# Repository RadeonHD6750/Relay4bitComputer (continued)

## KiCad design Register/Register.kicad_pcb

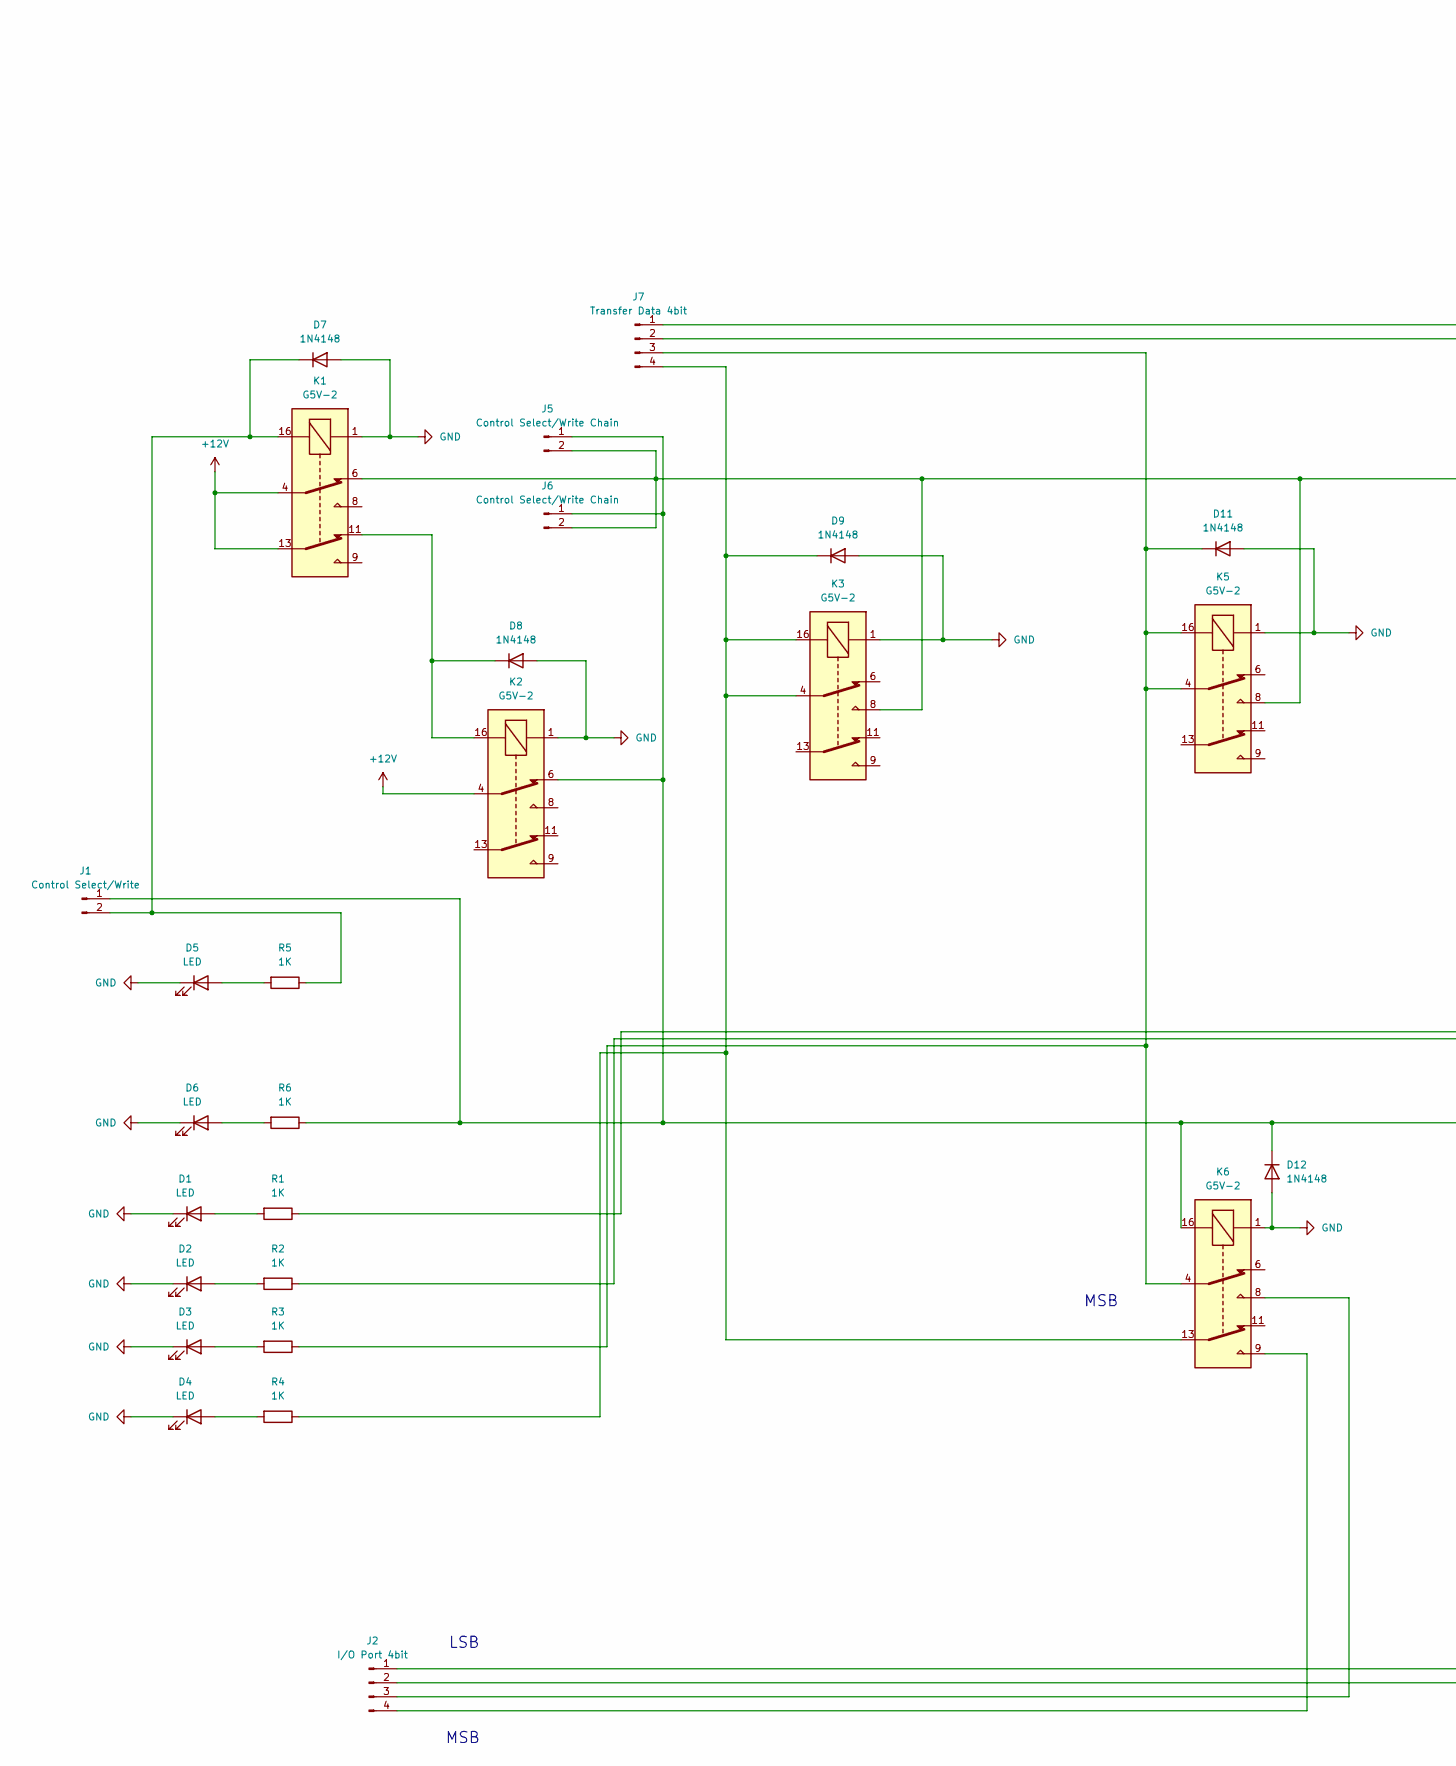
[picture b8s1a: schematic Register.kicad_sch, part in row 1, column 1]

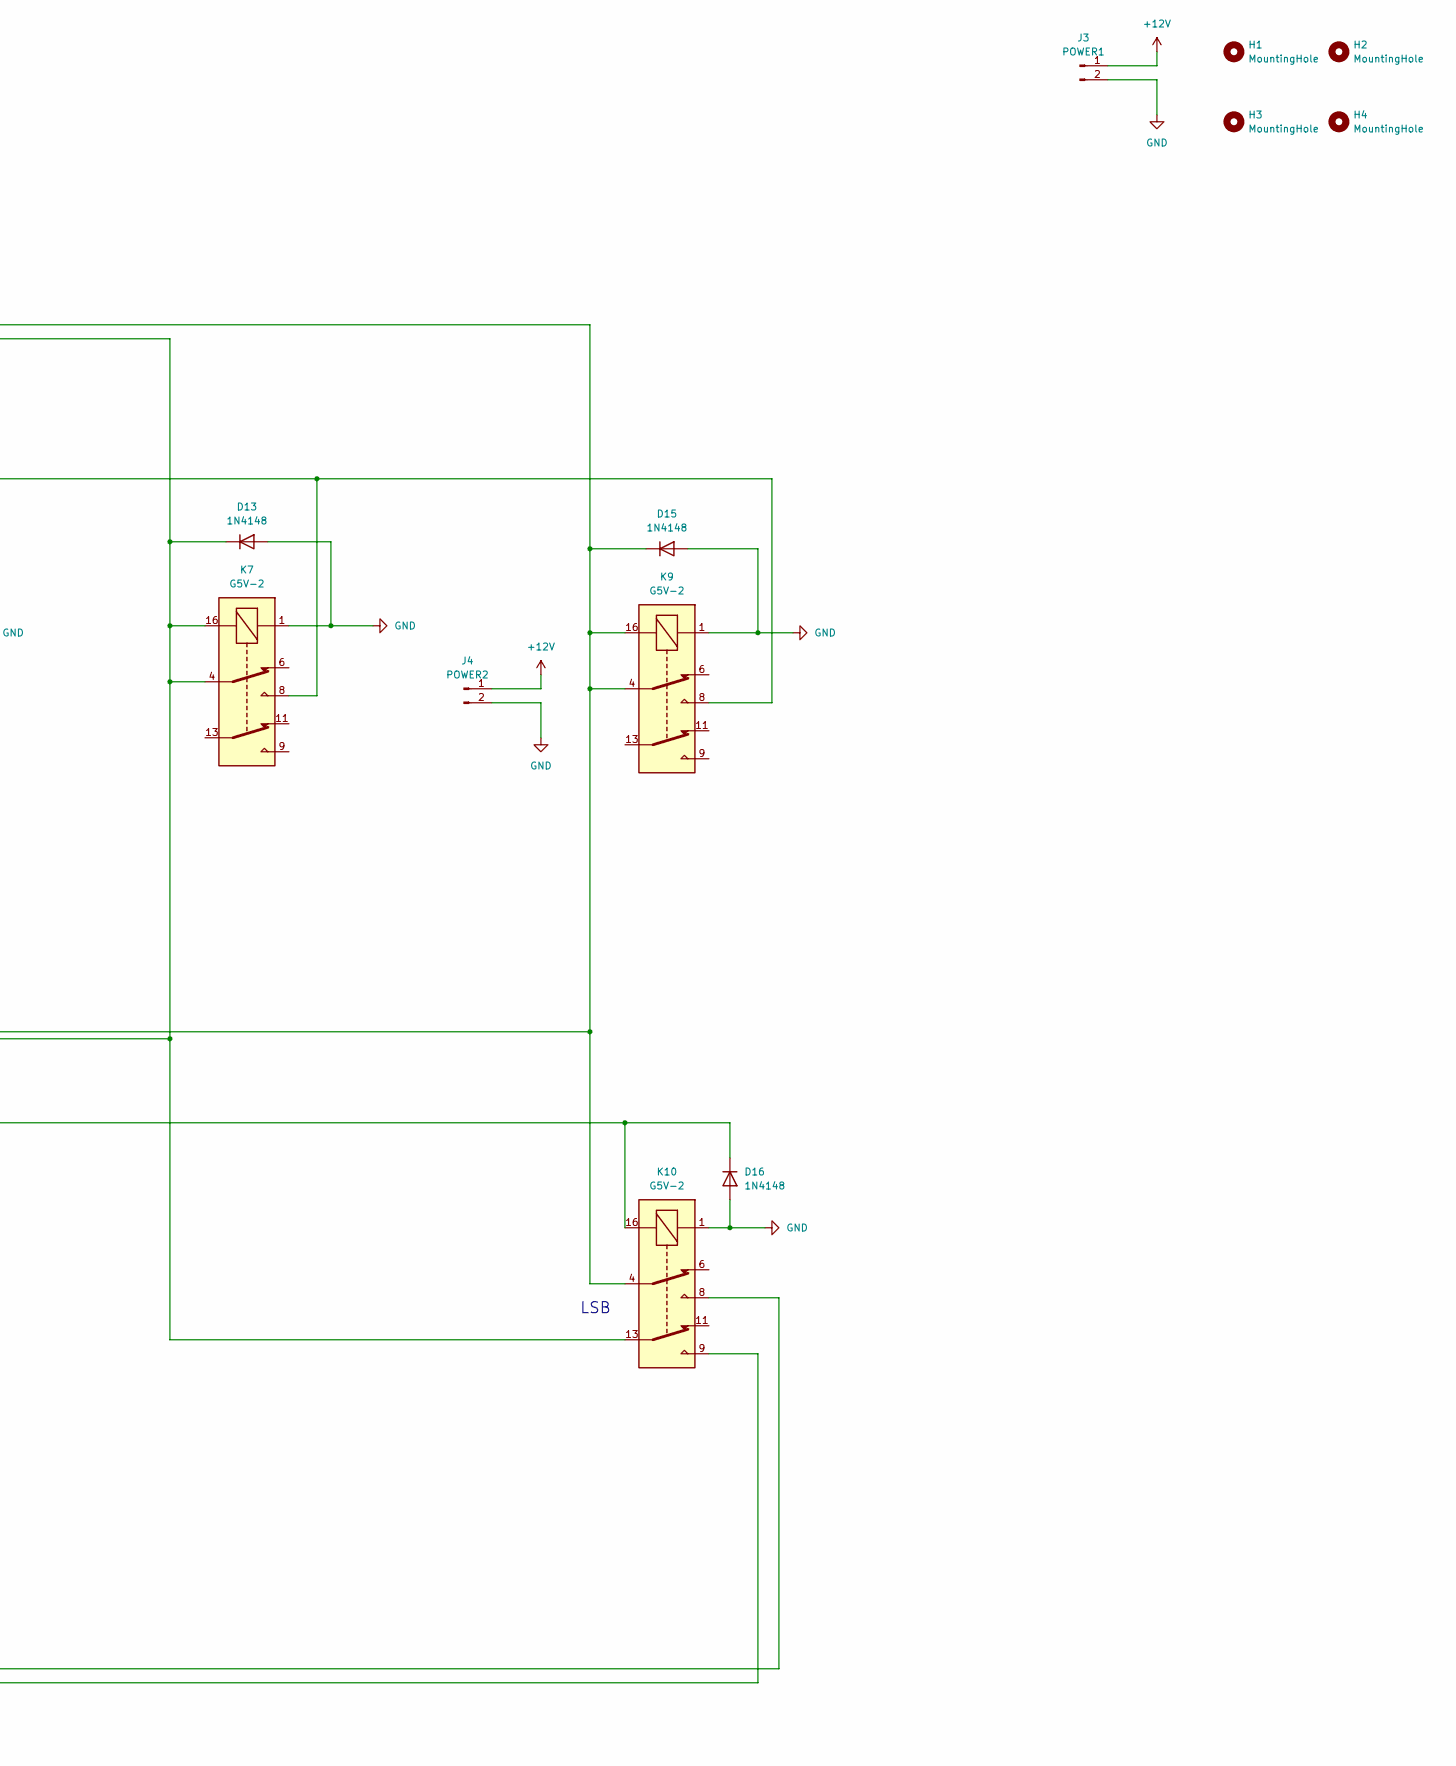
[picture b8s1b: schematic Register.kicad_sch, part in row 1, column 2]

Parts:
D1, D2, D3, D4, D5, D6: LED; LED_D5.0mm
D7, D8, D9, D11, D12, D13, D15, D16: 1N4148; D_DO-35_SOD27_P7.62mm_Horizontal
H1, H2, H3, H4: MountingHole; MountingHole_3.2mm_M3
J1: Control Select/Write; PinHeader_1x02_P2.54mm_Vertical
J2: I/O Port 4bit; PinHeader_1x04_P2.54mm_Vertical
J3: POWER1; PinHeader_1x02_P2.54mm_Vertical
J4: POWER2; PinHeader_1x02_P2.54mm_Vertical
J5, J6: Control Select/Write Chain; PinHeader_1x02_P2.54mm_Vertical
J7: Transfer Data 4bit; PinHeader_1x04_P2.54mm_Vertical
K1, K2, K3, K5, K6, K7, K9, K10: G5V-2; Relay_DPDT_Omron_G5V-2
R1, R2, R3, R4, R5, R6: 1K; R_Axial_DIN0207_L6.3mm_D2.5mm_P10.16mm_Horizontal

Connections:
+12V: J3.1, J4.1, K1.4, K1.13, K2.4
GND: D1.1 (K), D2.1 (K), D3.1 (K), D4.1 (K), D5.1 (K), D6.1 (K), D7.2 (A), D8.2 (A), D9.2 (A), D11.2 (A), D12.2 (A), D13.2 (A), D15.2 (A), D16.2 (A), J3.2, J4.2, K1.1, K2.1, K3.1, K5.1, K6.1, K7.1, K9.1, K10.1
unnamed: D1.2 (A), R1.2
unnamed: D2.2 (A), R2.2
unnamed: D3.2 (A), R3.2
unnamed: D4.2 (A), R4.2
unnamed: D5.2 (A), R5.2
unnamed: D6.2 (A), R6.2
unnamed: D7.1 (K), J1.2, K1.16, R5.1
unnamed: D8.1 (K), K1.11, K2.16
unnamed: D9.1 (K), J7.4, K3.4, K3.16, K6.13, R4.1
unnamed: D11.1 (K), J7.3, K5.4, K5.16, K6.4, R3.1
unnamed: D12.1 (K), D16.1 (K), J1.1, J5.1, J6.1, K2.6, K6.16, K10.16, R6.1
unnamed: D13.1 (K), J7.2, K7.4, K7.16, K10.13, R2.1
unnamed: D15.1 (K), J7.1, K9.4, K9.16, K10.4, R1.1
unnamed: J2.1, K10.8
unnamed: J2.2, K10.9
unnamed: J2.3, K6.8
unnamed: J2.4, K6.9
unnamed: J5.2, J6.2, K1.6, K3.8, K5.8, K7.8, K9.8

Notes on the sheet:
LSB
MSB

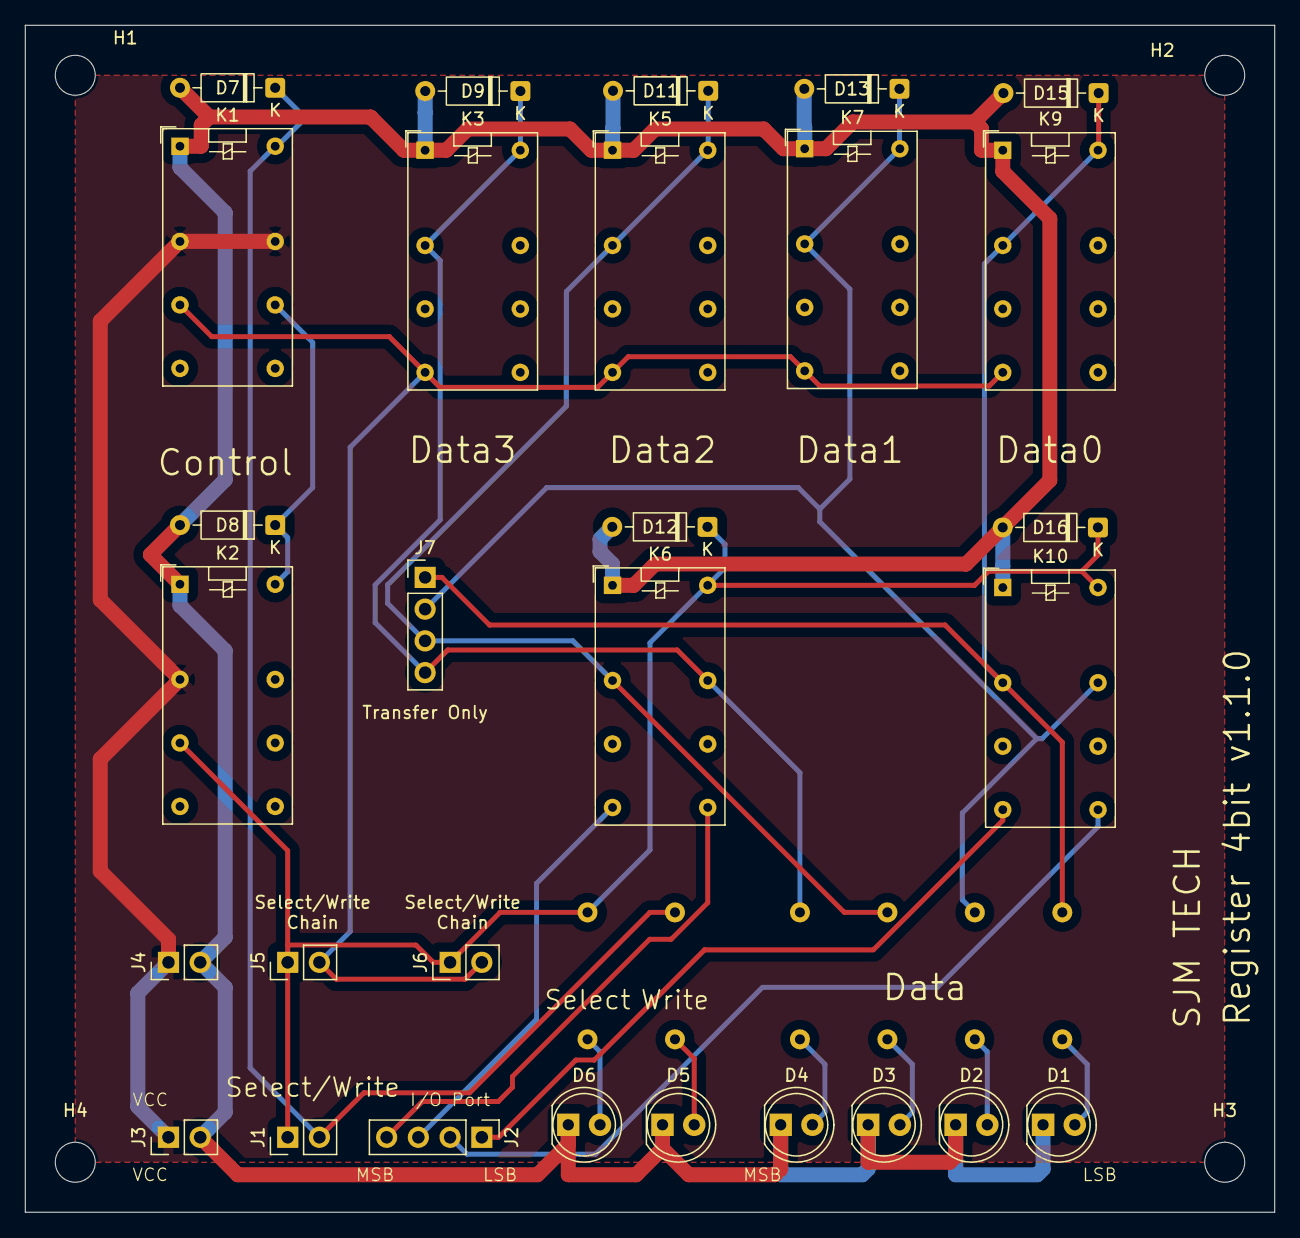
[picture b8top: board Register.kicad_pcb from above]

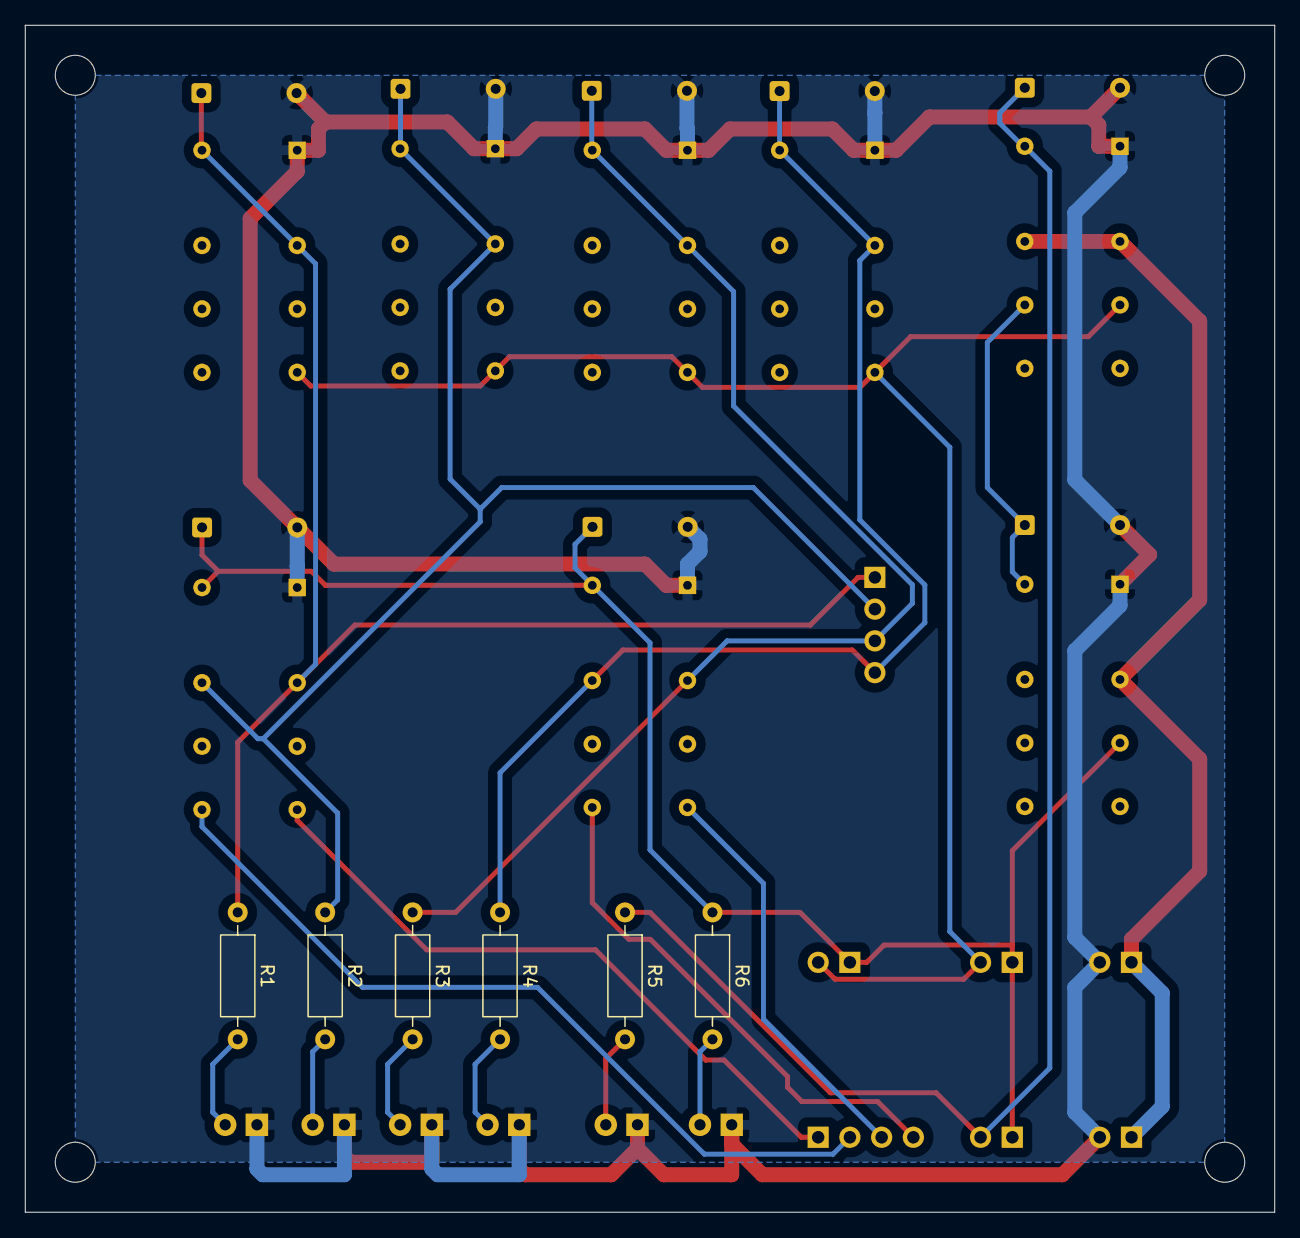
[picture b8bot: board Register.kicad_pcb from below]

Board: 2 copper layers, 100.0 x 95.0 mm, 39 parts (6 on the bottom side), 20 nets.

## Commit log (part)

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2026-04-28 2026-04-28
    초기설정
2026-04-29 2026-04-29
    8bit로 설계변경
2026-04-30 2026-04-30 설계변경
    4bit에서 8bit
2026-05-01 2026-05-01 제어신호 매트릭스
    인출단계, 해독단계, 실행단계 매트릭스 작성완료
2026-05-01 2026-05-01 참고자료
    참고자료
2026-05-04 2026-05-04 전가산기 시뮬
    전가산기 시뮬 2bit 짜리 완성
2026-05-06 2026-05-06 Full Adder
    전가산기 4bit짜리 설계 아트웤 해야 됨
2026-05-06 2026-05-06
    LED 추가
2026-05-07 2026-05-07 4bit Full Adder 완성
    4bit 전가산기 모듈 완성
2026-05-07 2026-05-07 다이오드 변경
    1N4148으로 변경
2026-05-08 2026-05-08
    다이오드 교체완료
2026-05-08 2026-05-08 자동배선
    자동배선
2026-05-08 2026-05-08 영역 채우기 완료
    영역 채우기 완료
2026-05-08 2026-05-08 Register 설계완료
    전가산기에 전력선 추가해야 됨.
    레지스터에 라우팅 해야 됨.
2026-05-08 2026-05-08 전가산기 작업
    마운트홀을 그냥 마운트로 변경
    전력단자 추가
2026-05-08 2026-05-08 가감산기
    가감산기 논리회로
2026-05-10 2026-05-10, 레지스터,디코더, ROM 완성
    레지스터 배선
    디코더 작업
    ROM 작업
2026-05-11 2026-05-11 서로 다른 클럭수 구현
    서로 다른 클럭수 구현 방법
2026-05-11 2026-05-11 카운터
    전가산기 + 레지스터 조합으로 만들 예정
2026-05-11 2026-05-11 MircoROM 통합
    인출단계 ROM을 실행ROM이랑 통합
2026-05-12 2026-05-12 Counter는 링카운터로
    32개만 있으면 된다.
2026-05-12 2026-05-12 ring counter 4bit module
    링카운터로 만들긴 했는데 회로동작 검증이 필요할듯
2026-05-12 2026-05-12 배선정리
    배선정리
2026-05-12 2026-05-12 1차 주문
    FA, REG, Decoder, Matrix
2026-05-25 2026-05-25
    Full Adder 실험 결과, 전력이 연산결과에 따라 일정하지 않음. 따라서 Enabler를 통하여 다시 12V로 쏴주는 것이 필요함. 뭐 논리기능으로도 활성 비활성도 같이 겸할 수 있으니 다행인가?
2026-05-25 2026-05-25 3-8 디코더 문제발견
    디코더 입력단자 디버그 LED들이 순서가 뒤바껴있음. 그나마 기능 자체는 정상동작함. 입력단 LED들만 이상한 순서로 되어 있고, 회로도 자체는 문제없음. 즉, 아트웤에서 풋프린트 배치가 잘못된거임. 기능 자체를 이상없으니 입력단 LED만 제외하고 사용하면 될듯. 그대로 혹시 몰라 일단 아트웤 배선 초기화해둠.
2026-05-25 2026-05-25
    일지기록 시작
2026-05-25 2026-05-25 레지스터 동작점검 결과
    동작에는 문제없으나 Read/Write 공유를 할 수 없어 4Nbit를 만들 때 N개의 Read/Write를 연결해야 한다. 따라서 체인할 수 있게 단자 추가함.
2026-05-27 2026-05-27
    Select/Write 로직을 수행할 릴레이를 절약하기 위해 공통선으로 묶고 공유 시키기
2026-05-27 2026-05-27
    카운터는 그냥 레지스터와 가산기 활용해서 동기식으로 구현하고, 로직블럭은 4bit 단위로 쪼개서 구현
2026-05-28 2026-05-28
    레지스터에 기억기능을 비활성화하여 단순 전송여부만 결정할 트랜스퍼 기능 추가, 논리연산을 수행할 로직블럭 제작
2026-05-29 2026-05-29
    이왕 하는 거, 명령어 16개로 증설
    명령어 매트릭스 수정해야됨
    로직블럭 아트웍 해야됨
2026-05-30 2026-05-31
    로직블럭 아트웍 하는 중
2026-05-31 2026-05-31
    ALU에 디버그를 위한 LED가 필요
2026-06-01 2026-06-01
    ALU 플래그 라벨 추가
2026-06-03 2026-06-03
    산술장치 분리, ALU 설계 완료
2026-06-04 2026-06-04
    BIU까지는 만들어야 결합할듯
2026-06-05 2026-06-05
    BIU 시작
2026-06-07 2026-06-07
    BIU 배선 해야 됨
2026-06-09 2026-06-09
    BIU 초안 완료
2026-06-10 2026-06-10
    Register, Arithmetic, LogicBlock, ALU 라우팅 완료, 거버 생성은 해야 됨
2026-06-11 2026-06-11
    8만원 정도로 PCB 주문
2026-06-16 2026-06-16
    동일된 사이클로 명령어를 처리하기 위한 회로도 작성
2026-06-16 타이밍 단자 추가
    타이밍 단자 추가
2026-06-18 2026-06-18
    회로 점검
2026-06-28 타이밍 보강해야 함
    지금 타이밍2스텝인데 4스텝까지도 생각해야됨
2026-06-30 2026-06-30
    어느 정도는 된 것 같은데 좀 더 봐야 할듯
